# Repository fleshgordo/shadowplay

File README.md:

---------------------------------------------------------------

TIAN shadowplay - robotic light installation

Copyright Gordan Savicic 2012.

This program is free software: you can redistribute it
and/or modify it under the terms of the GNU Lesser General
Public License as published by the Free Software Foundation,
either version 3 of the License, or (at your option) any 
later version.

This program is distributed in the hope that it will be
useful, but WITHOUT ANY WARRANTY; without even the implied
warranty of MERCHANTABILITY or FITNESS FOR A PARTICULAR
PURPOSE.  See the GNU Lesser General Public License for more
details.

You should have received a copy of the GNU Lesser General
Public License along with this program.  If not, see
<http://www.gnu.org/licenses/>.

---------------------------------------------------------------

Shadowplay is a light installation for TIAN's chandelier
(www.tian-vienna.com) 
Concept & Production by design agency STRUKT Vienna 
(www.strukt.com) 
Light Design & Hardware by Gordan Savicic 
(www.yugo.at)

Two pan/tilt robotic units equipped with 10W LEDs were
installed inside the chandelier.  Through algorithmic
controlling of light positioning and brightness (PWM), they
produce different shadows along the ceiling and walls,
inviting the participator to experience various
patterns and reflections which subsequently form
their own spatial narrative.

---------------------------------------------------------------

Main hardware parts (see /schematics folder for CAD files):

* Arduino Mega (www.arduino.cc/en/Main/ArduinoBoardMega)
* Wifi Shield (www.arduino.cc/en/Main/ArduinoWiFiShield)
* 10W warm-white LEDs (www.reichelt.de) Constant Current
* Drivers BUCK (www.led-tech.de) 
* Glass Lenses (Lens Reflector 10W www.hero-ledstore.com)
* Custom PCB 
* Custom Aluminium pan/tilt unit (see /cnc folder for drawings)
  based on Lynx B Pan and Tilt kit (www.lynxmotion.com)

Software:

* written in C (see /firmware folder)

---------------------------------------------------------------

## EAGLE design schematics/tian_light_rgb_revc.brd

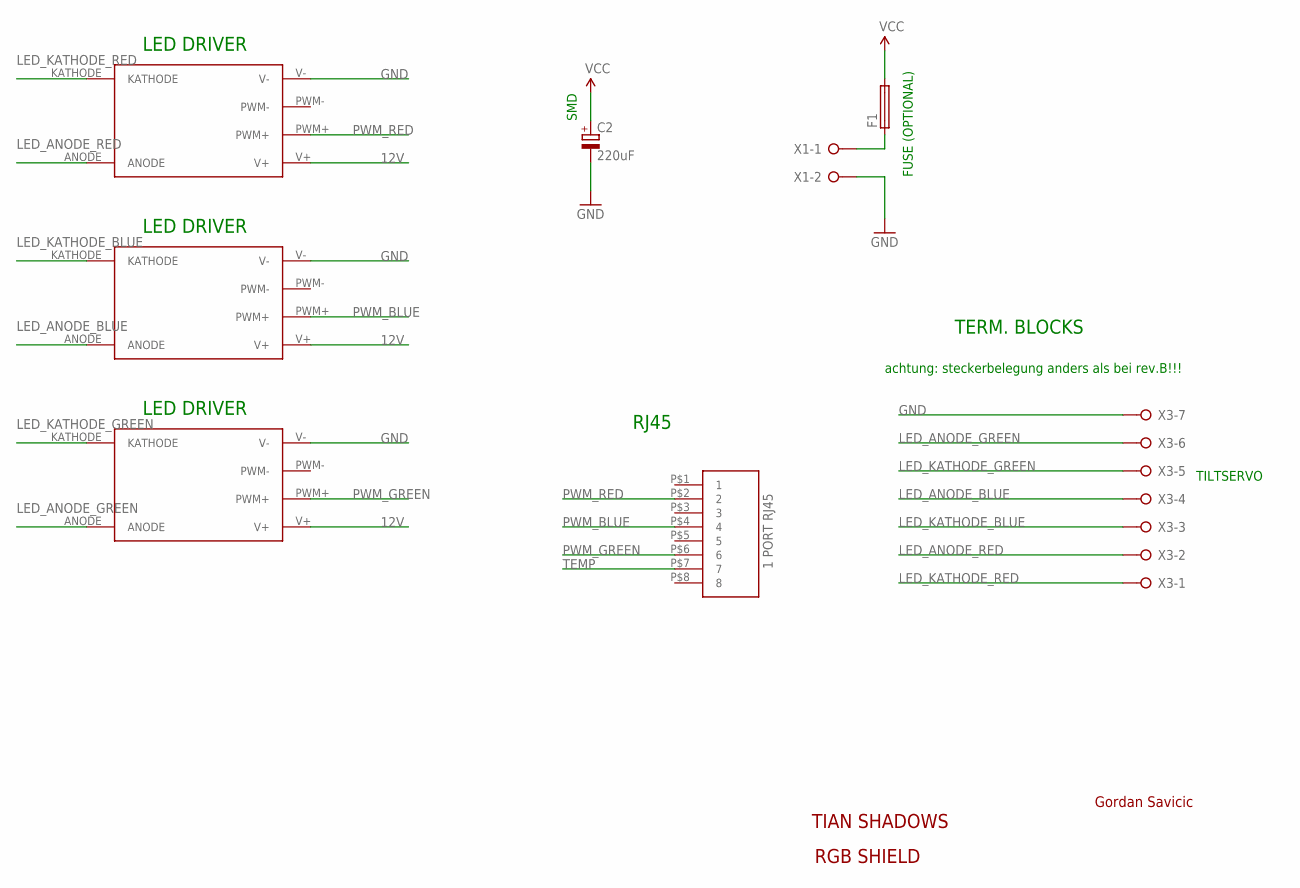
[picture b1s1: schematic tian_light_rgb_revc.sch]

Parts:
C2: 220uF; PANASONIC_F
F1: SH22,5
U$1, U$2, U$3: BUCK_LED_DRIVER
U$5: 1PORT_ETHERNET
X1: W237-02P; W237-132
X3: W237-07P; W237-7P

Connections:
12V: C2.+, F1.2, U$1.V+, U$2.V+, U$3.V+
GND: C2.-, U$1.V-, U$2.V-, U$3.V-, X1.2, X3.7
LED_ANODE_BLUE: U$2.ANODE, X3.4
LED_ANODE_GREEN: U$3.ANODE, X3.6
LED_ANODE_RED: U$1.ANODE, X3.2
LED_KATHODE_BLUE: U$2.KATHODE, X3.3
LED_KATHODE_GREEN: U$3.KATHODE, X3.5
LED_KATHODE_RED: U$1.KATHODE, X3.1
unnamed: F1.1, X1.1
PWM_BLUE: U$2.PWM+, U$5.P$4 (4)
PWM_GREEN: U$3.PWM+, U$5.P$6 (6)
PWM_RED: U$1.PWM+, U$5.P$2 (2)
TEMP: U$5.P$7 (7)

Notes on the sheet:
TILTSERVO
TIAN SHADOWS
RGB SHIELD
Gordan Savicic
RJ45
TERM. BLOCKS
LED DRIVER
achtung: steckerbelegung anders als bei rev.B!!!
FUSE (OPTIONAL)
SMD

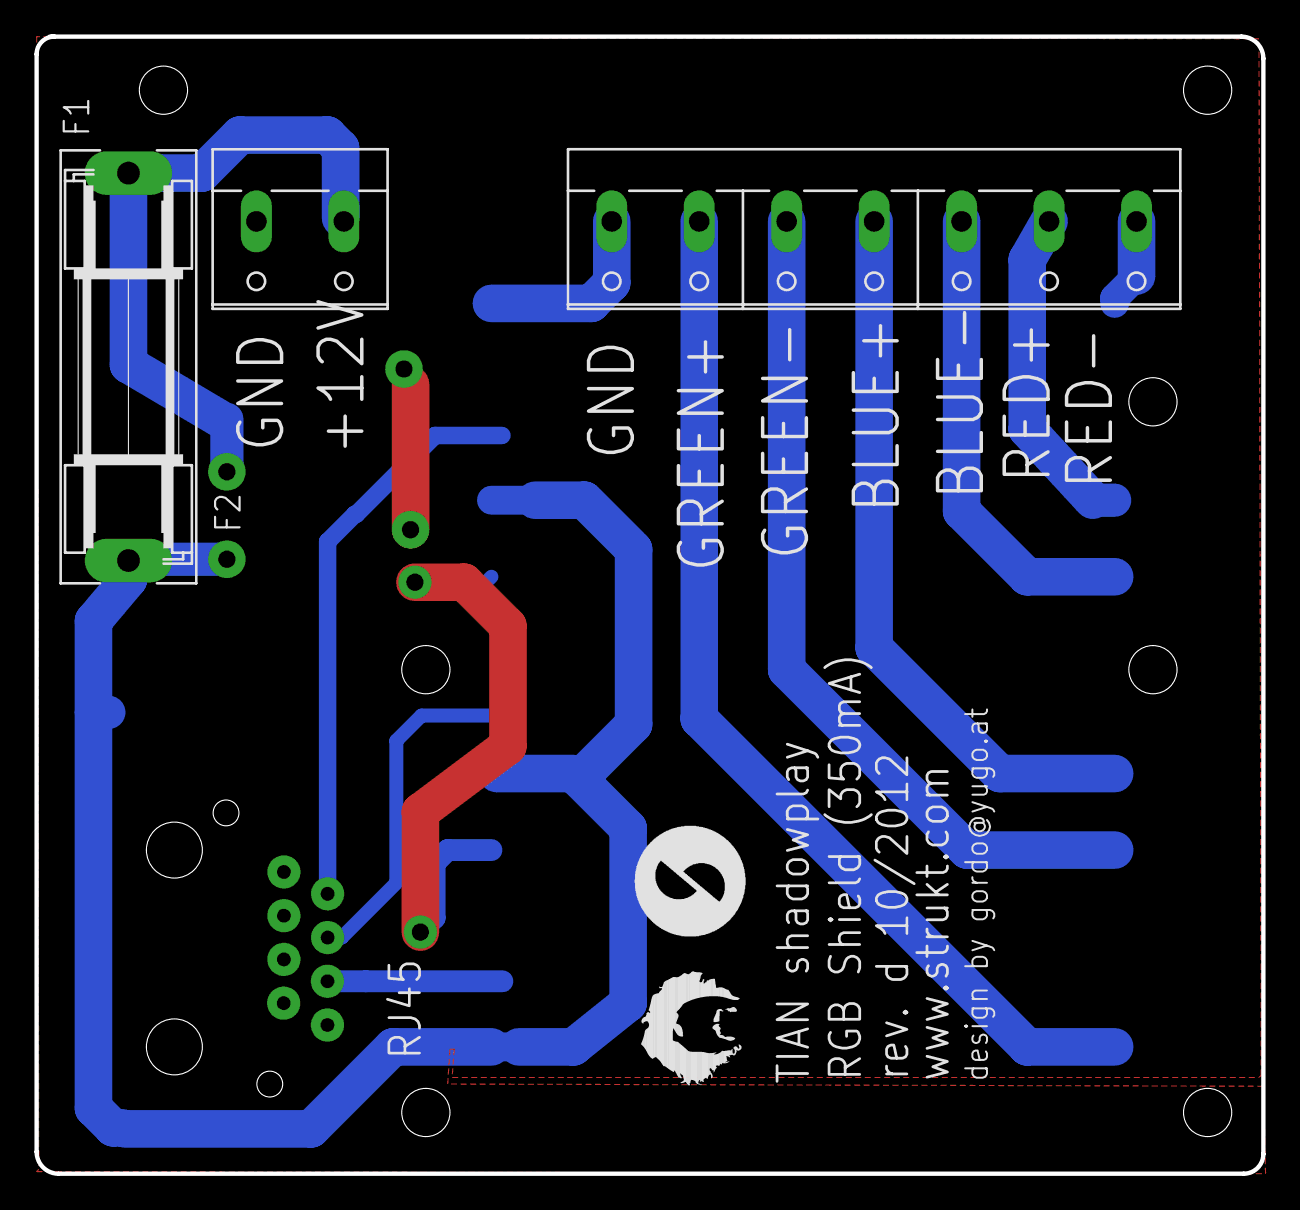
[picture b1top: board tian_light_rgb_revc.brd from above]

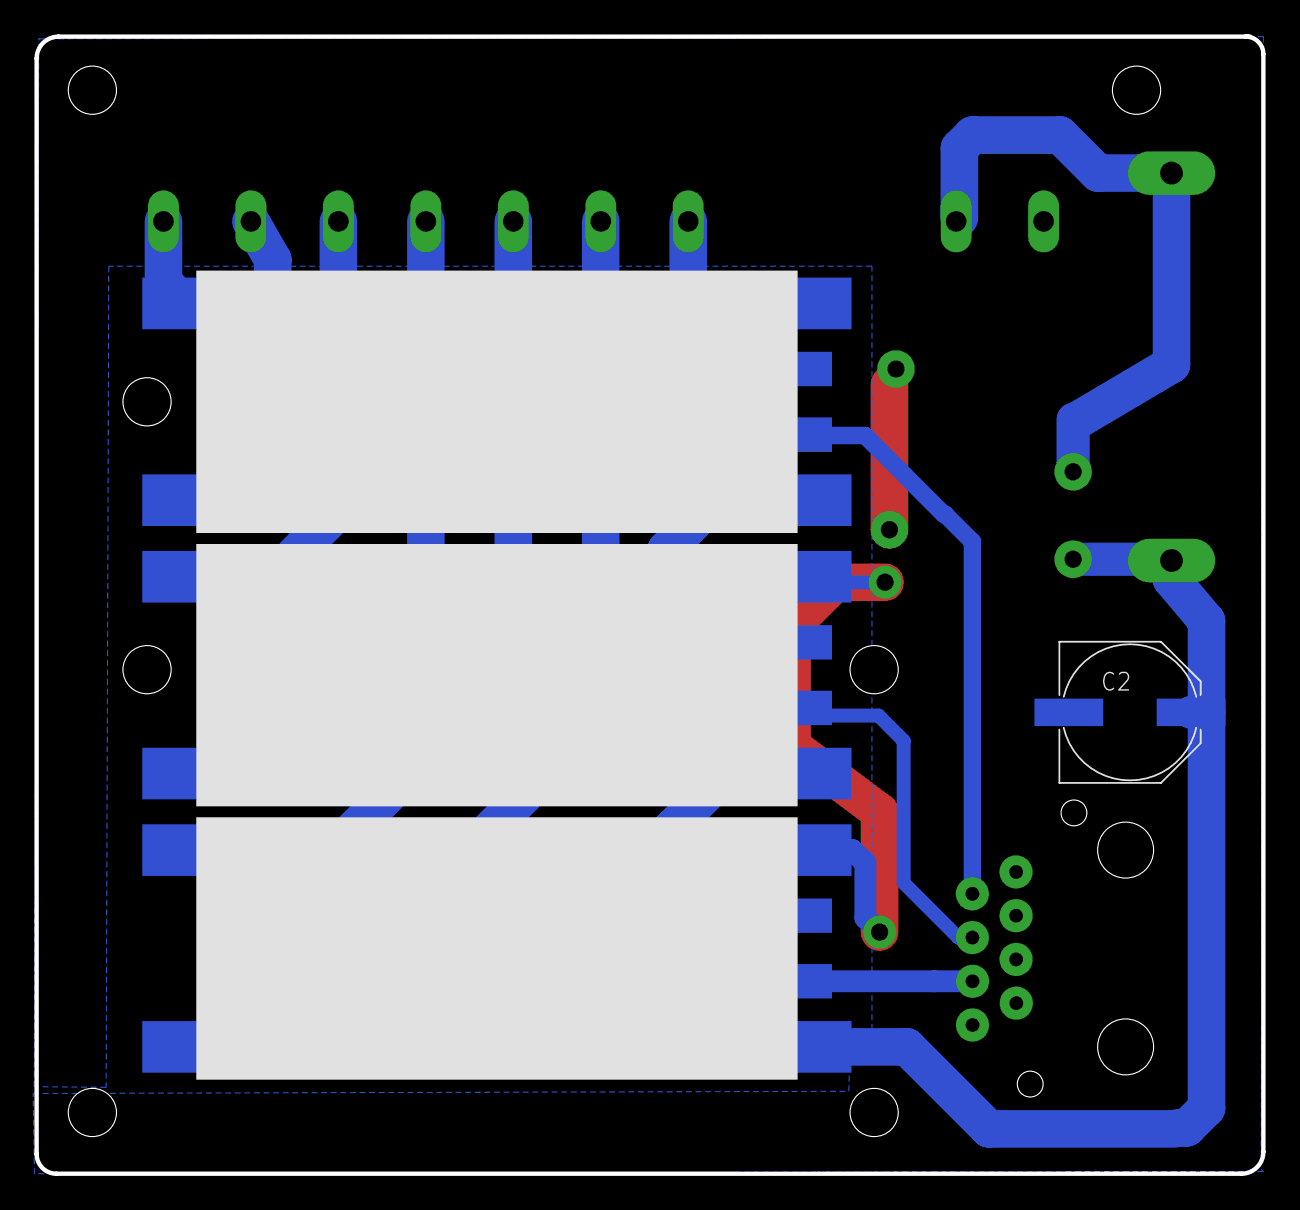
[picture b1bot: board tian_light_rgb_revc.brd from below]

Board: 2 copper layers, 71.2 x 66.0 mm, 8 parts (5 on the bottom side), 12 nets.

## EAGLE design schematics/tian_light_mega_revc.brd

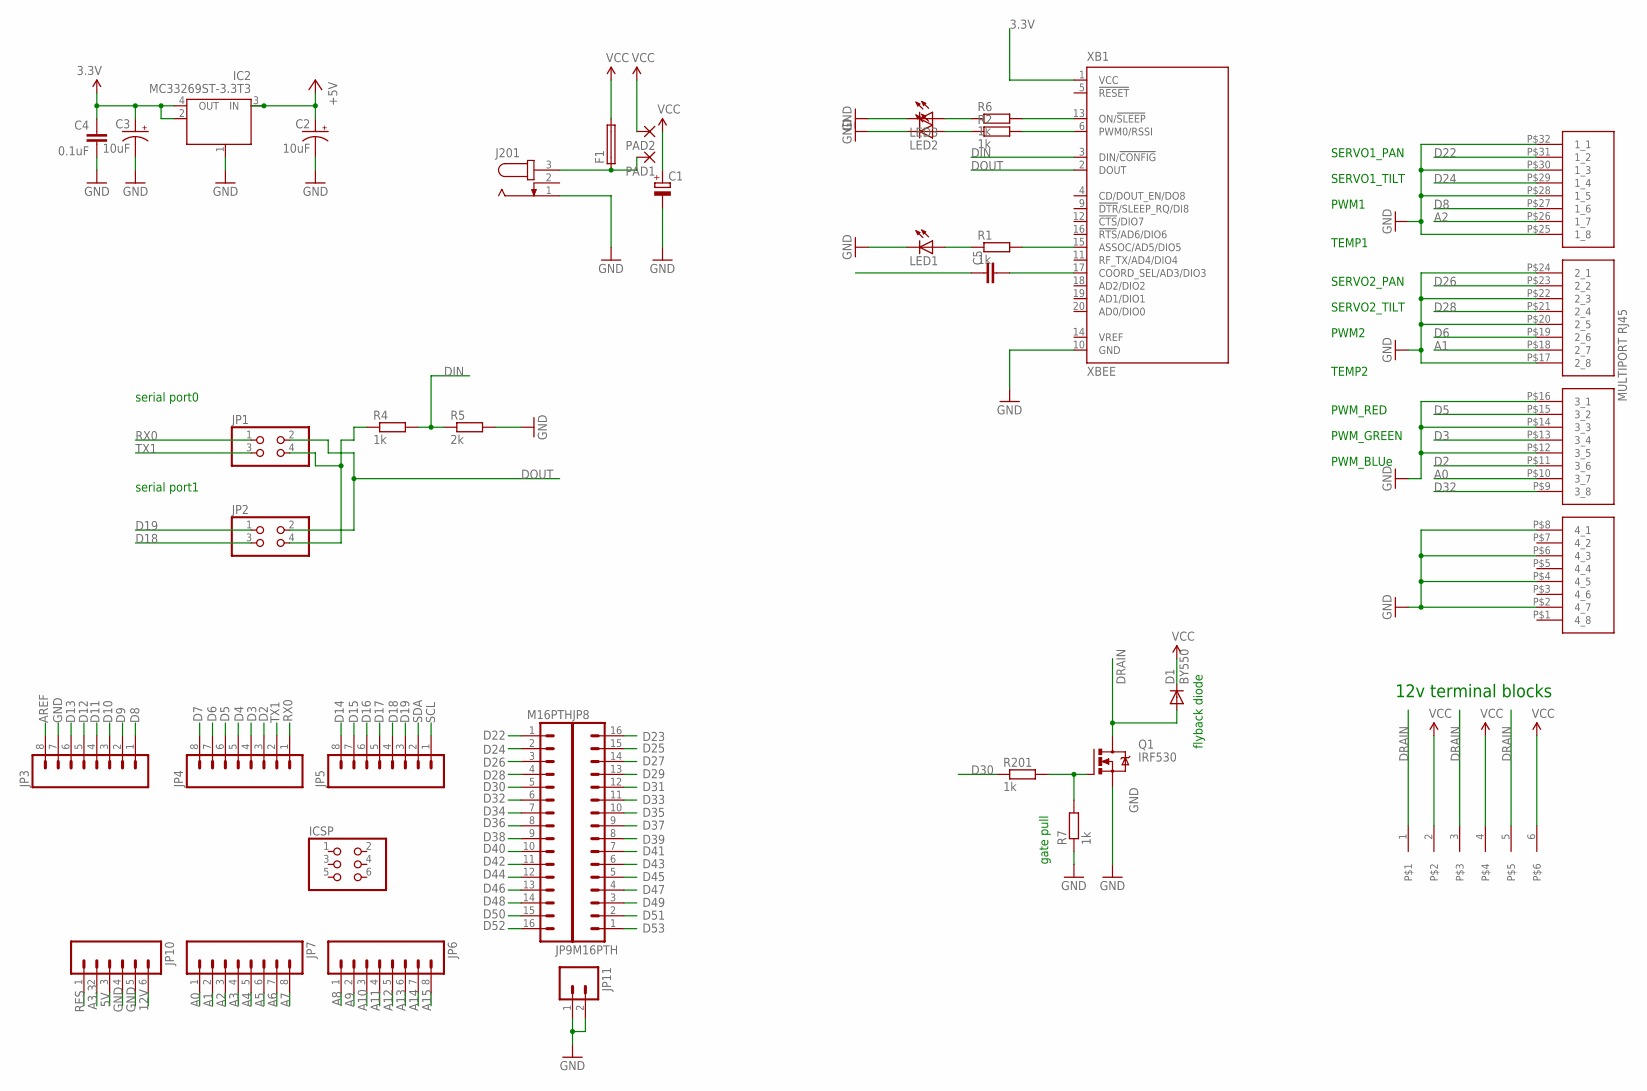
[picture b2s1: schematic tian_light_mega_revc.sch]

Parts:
C1: CPOL-EU153CLV-0605; 153CLV-0605
C2, C3: 10uF; EIA3216
C4: 0.1uF; 0603-CAP
C5: C-EUC0805; C0805
D1: BY550; DO27-15
F1: SH22,5
IC2: MC33269ST-3.3T3; SOT223
ICSP: PINHD-2X3; 2X03
J201: JACK-PLUG0; SPC4077
JP1, JP2: PINHD-2X2; 2X02
JP3, JP4, JP5, JP6, JP7: M08LONGPADS; 1X08_LONGPADS
JP8, JP9: M16PTH; 1X16
JP10: M06SIP; 1X06
JP11: M02LOCK; 1X02_LOCK
LED1, LED2, LED3: LEDSML1206; SML1206
PAD1, PAD2: 2,15/1,0
PORT201: 4PORT_ETHERNET
Q1: IRF530; TO220BV
R1, R2, R4, R6, R7, R201: 1k; M1206
R5: 2k; M1206
U$3: MFKDSP6-5.08; PHONEIX
XB1: XBEE

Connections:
3.3V: C3.A (+), C4.1, IC2.2 (OUT), IC2.4 (OUT), XB1.1 (VCC)
5V: C2.A (+), IC2.3 (IN), JP10.3
12V: C1.+, F1.2, JP10.6, PAD2.1, U$3.2, U$3.4, U$3.6
A0: JP7.1, PORT201.P$10 (3_7)
A1: JP7.2, PORT201.P$18 (2_7)
A2: JP7.3, PORT201.P$26 (1_7)
A3: JP7.4
A3.3: JP10.2
A4: JP7.5
A5: JP7.6
A6: JP7.7
A7: JP7.8
A8: JP6.1
A9: JP6.2
A10: JP6.3
A11: JP6.4
A12: JP6.5
A13: JP6.6
A14: JP6.7
A15: JP6.8
AREF: JP3.8
D2: JP4.3, PORT201.P$11 (3_6)
D3: JP4.4, PORT201.P$13 (3_4)
D4: JP4.5
D5: JP4.6, PORT201.P$15 (3_2)
D6: JP4.7, PORT201.P$19 (2_6)
D7: JP4.8
D8: JP3.1, PORT201.P$27 (1_6)
D9: JP3.2
D10: JP3.3
D11: JP3.4
D12: JP3.5
D13: JP3.6
D14: JP5.8
D15: JP5.7
D16: JP5.6
D17: JP5.5
D18: JP2.3, JP5.4
D19: JP2.1, JP5.3
D22: JP9.1, PORT201.P$31 (1_2)
D23: JP8.16
D24: JP9.2, PORT201.P$29 (1_4)
D25: JP8.15
D26: JP9.3, PORT201.P$23 (2_2)
D27: JP8.14
D28: JP9.4, PORT201.P$21 (2_4)
D29: JP8.13
D30: JP9.5, R201.1
D31: JP8.12
D32: JP9.6, PORT201.P$9 (3_8)
D33: JP8.11
D34: JP9.7
D35: JP8.10
D36: JP9.8
D37: JP8.9
D38: JP9.9
D39: JP8.8
D40: JP9.10
D41: JP8.7
D42: JP9.11
D43: JP8.6
D44: JP9.12
D45: JP8.5
D46: JP9.13
D47: JP8.4
D48: JP9.14
D49: JP8.3
D50: JP9.15
D51: JP8.2
D52: JP9.16
D53: JP8.1
DIN: R4.2, R5.1, XB1.3 (DIN/!CONFIG)
DOUT: JP1.2, JP2.2, XB1.2 (DOUT)
DRAIN: D1.A, Q1.D, U$3.1, U$3.3, U$3.5
GND: C1.-, C2.C (-), C3.C (-), C4.2, IC2.1 (GND/ADJ), J201.1, JP3.7, JP10.4, JP10.5, JP11.1, JP11.2, LED1.C, LED2.C, LED3.C, PORT201.P$2 (4_7), PORT201.P$4 (4_5), PORT201.P$6 (4_3), PORT201.P$8 (4_1), PORT201.P$12 (3_5), PORT201.P$14 (3_3), PORT201.P$16 (3_1), PORT201.P$17 (2_8), PORT201.P$20 (2_5), PORT201.P$22 (2_3), PORT201.P$24 (2_1), PORT201.P$25 (1_8), PORT201.P$28 (1_5), PORT201.P$30 (1_3), PORT201.P$32 (1_1), Q1.S, R5.2, R7.1, XB1.10 (GND)
unnamed: JP1.4, JP2.4, R4.1
unnamed: LED1.A, R1.1
unnamed: Q1.G, R7.2, R201.2
unnamed: R1.2, XB1.15 (ASSOC/AD5/DIO5)
unnamed: R6.2, XB1.13 (ON/!SLEEP)
unnamed: LED2.A, R2.1
unnamed: R2.2, XB1.6 (PWM0/RSSI)
unnamed: LED3.A, R6.1
unnamed: C5.2, XB1.17 (COORD_SEL/AD3/DIO3)
unnamed: F1.1, J201.3, PAD1.1
RES: C5.1, JP10.1
RX0: JP1.1, JP4.1
SCL: JP5.1
SDA: JP5.2
TX1: JP1.3, JP4.2
VCC: D1.C

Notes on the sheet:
12v terminal blocks
SERVO1_PAN
SERVO1_TILT
PWM1
TEMP1
SERVO2_PAN
SERVO2_TILT
PWM2
TEMP2
PWM_RED
PWM_GREEN
PWM_BLUe
flyback diode
gate pull
serial port1
serial port0

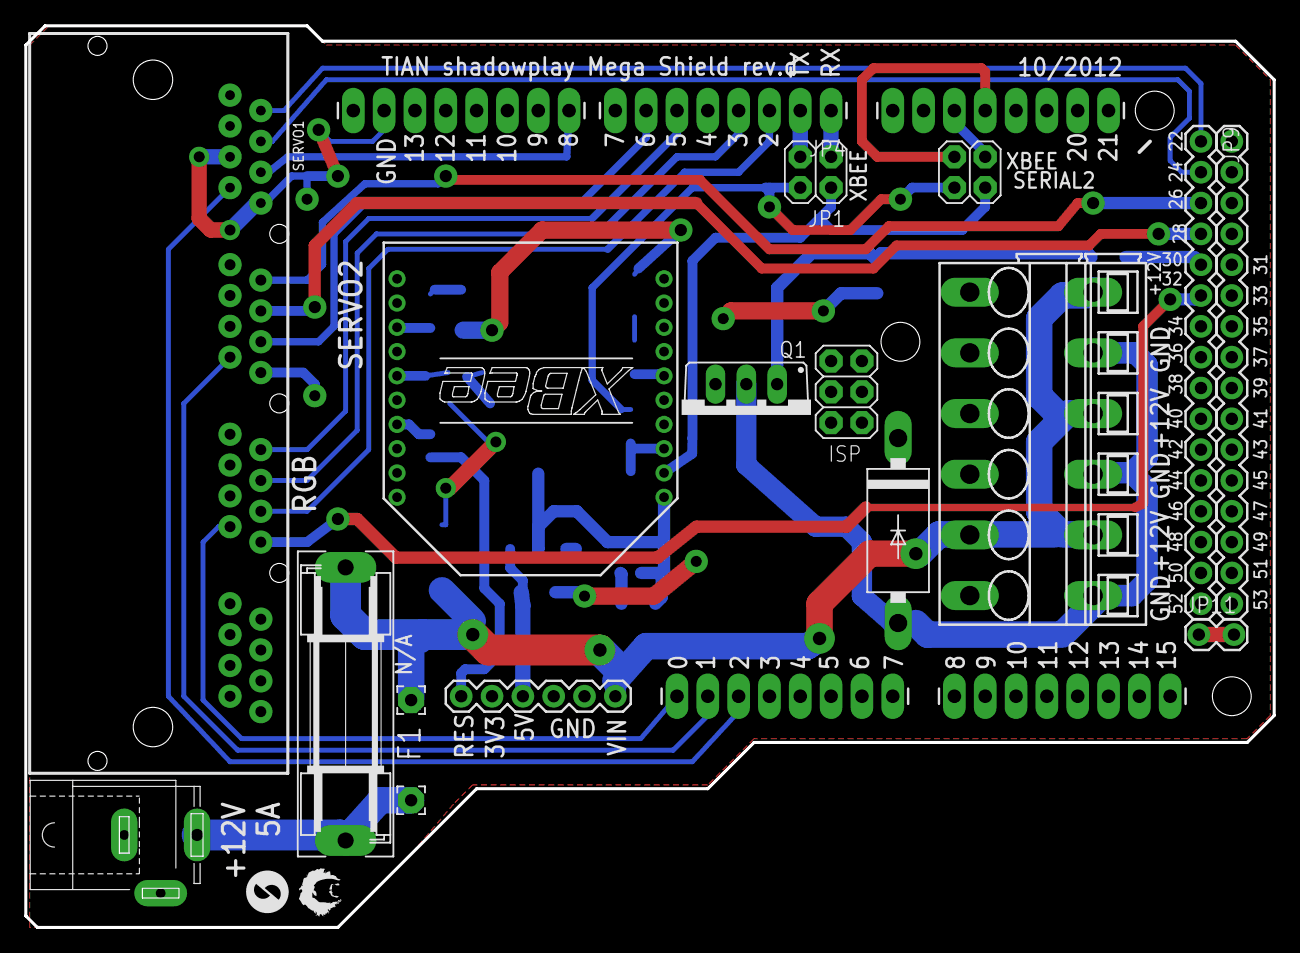
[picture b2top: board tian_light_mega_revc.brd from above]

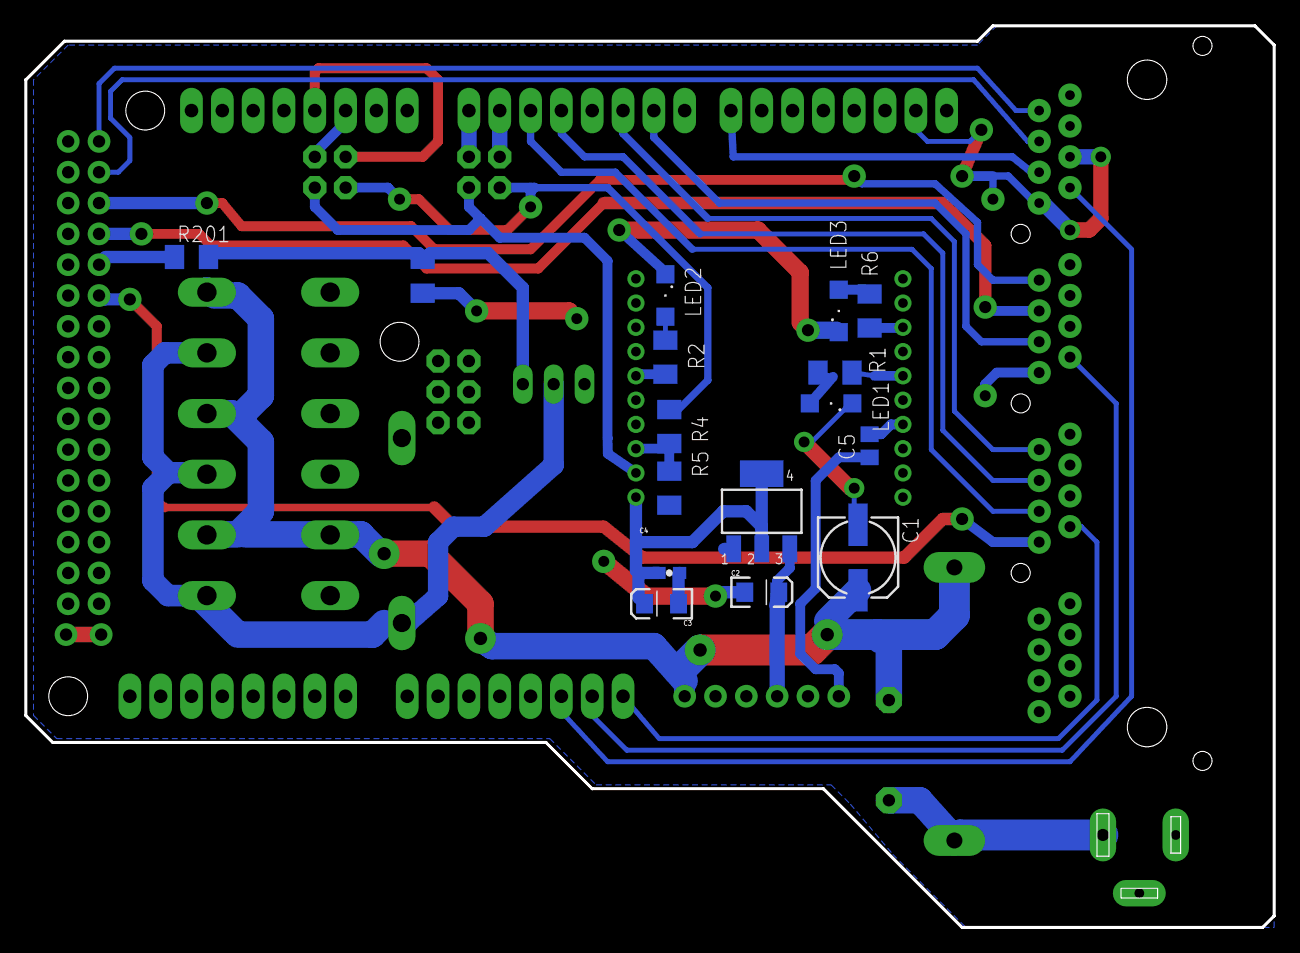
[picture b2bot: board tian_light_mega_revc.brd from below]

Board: 2 copper layers, 102.9 x 74.3 mm, 37 parts (16 on the bottom side), 36 nets.

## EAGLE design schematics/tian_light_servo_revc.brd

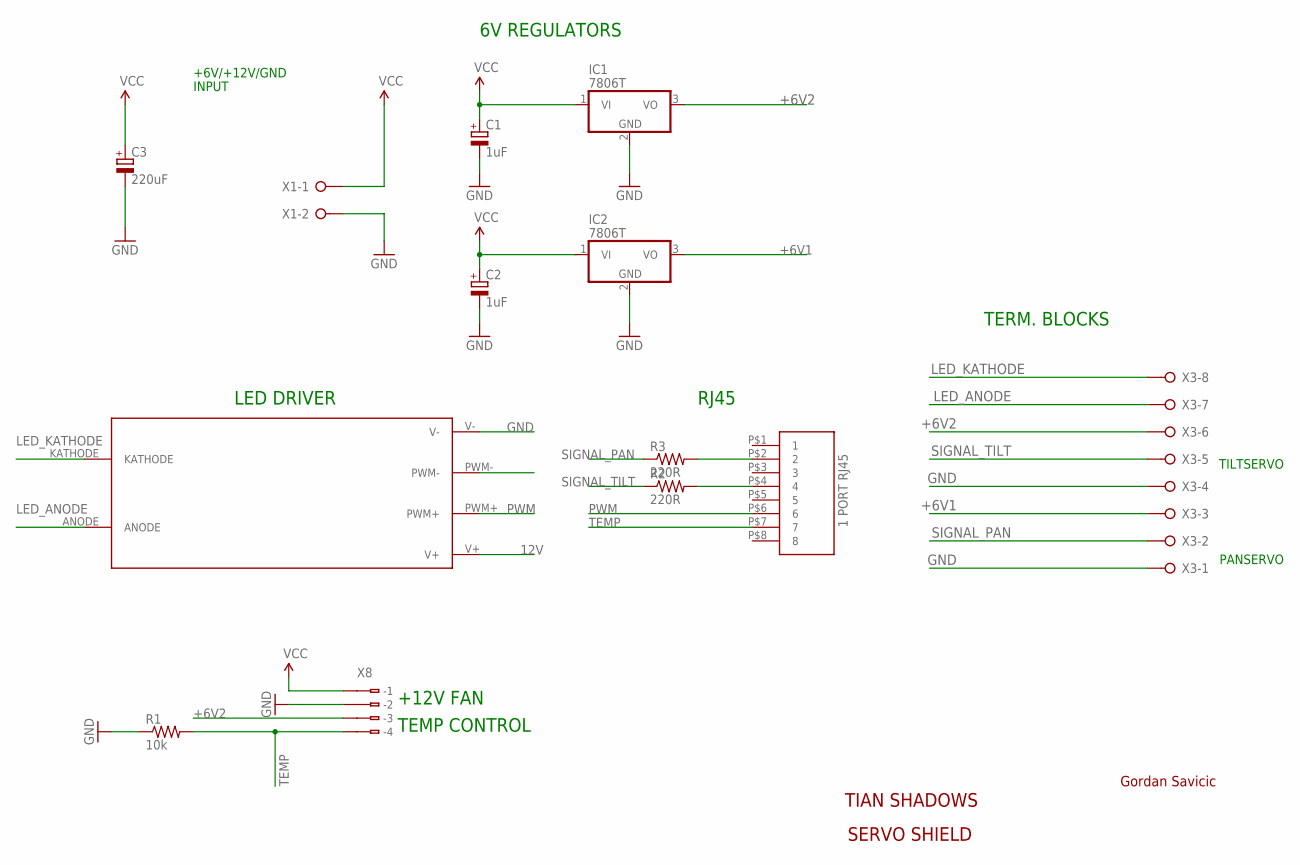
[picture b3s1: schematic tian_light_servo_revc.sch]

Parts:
C1, C2: 1uF; SMC_C
C3: 220uF; 153CLV-0605
IC1, IC2: 7806T; TO220H
R1: 10k; 1206
R2, R3: 220R; 1206
U$1: BUCK_LED_DRIVER
U$5: 1PORT_ETHERNET
X1: W237-02P; W237-132
X3: W237-08P; W237-8P
X8: 233-104

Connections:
12V: C1.+, C2.+, C3.+, IC1.1 (VI), IC2.1 (VI), U$1.V+, X1.1, X8.B1 (B-1)
+6V1: IC2.3 (VO), X3.3
+6V2: IC1.3 (VO), X3.6, X8.B3 (B-3)
GND: C1.-, C2.-, C3.-, IC1.2 (GND), IC2.2 (GND), R1.1, U$1.V-, X1.2, X3.1, X3.4, X8.B2 (B-2)
LED_ANODE: U$1.ANODE, X3.7
LED_KATHODE: U$1.KATHODE, X3.8
unnamed: R2.2, U$5.P$4 (4)
unnamed: R3.2, U$5.P$2 (2)
PWM: U$1.PWM+, U$5.P$6 (6)
SIGNAL_PAN: R3.1, X3.2
SIGNAL_TILT: R2.1, X3.5
TEMP: R1.2, U$5.P$7 (7), X8.B4 (B-4)

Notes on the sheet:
+6V/+12V/GND
INPUT
+12V FAN
TEMP CONTROL
PANSERVO
TILTSERVO
TIAN SHADOWS
SERVO SHIELD
Gordan Savicic
6V REGULATORS
RJ45
TERM. BLOCKS
LED DRIVER

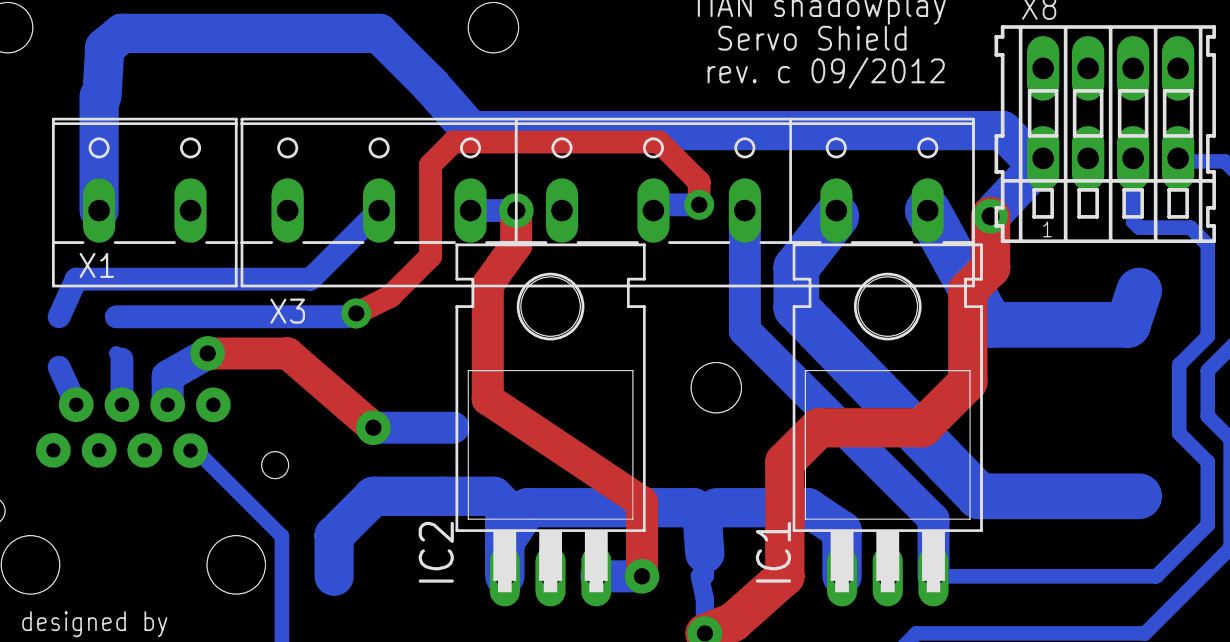
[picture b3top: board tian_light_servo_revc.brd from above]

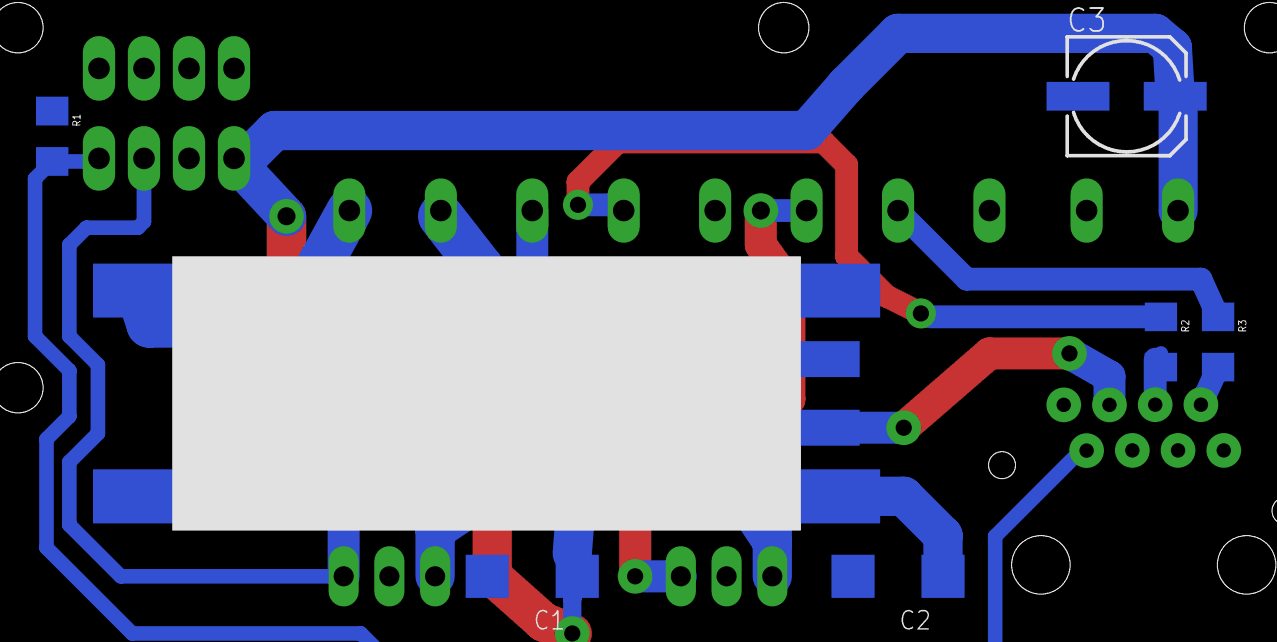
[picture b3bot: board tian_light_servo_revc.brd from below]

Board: 2 copper layers, 13 parts (8 on the bottom side), 12 nets.

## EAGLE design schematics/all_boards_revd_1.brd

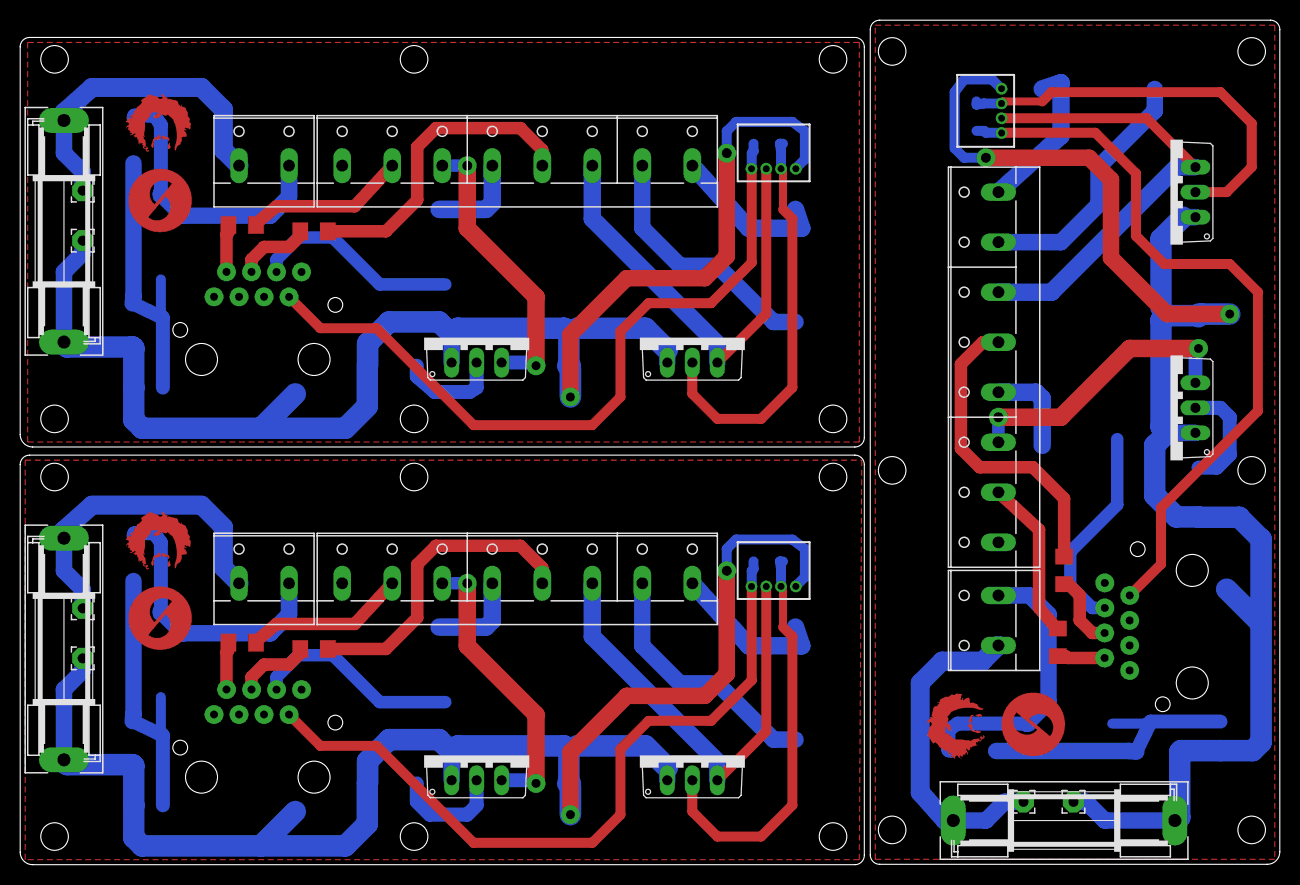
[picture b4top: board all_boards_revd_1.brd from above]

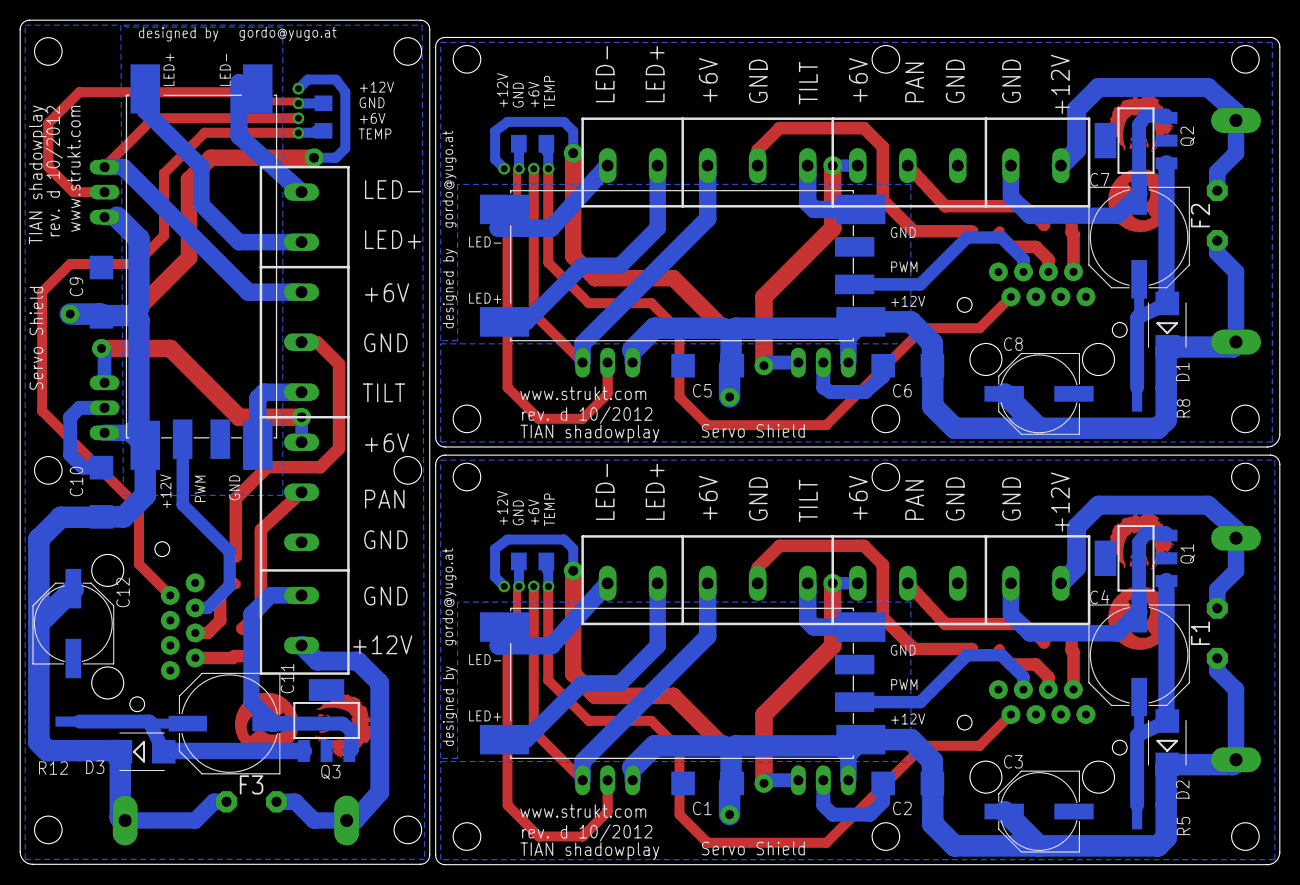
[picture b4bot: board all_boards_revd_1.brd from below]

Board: 2 copper layers, 127.9 x 85.8 mm, 60 parts (30 on the bottom side), 45 nets.

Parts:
C1, C2, C5, C6, C9, C10: 1uF; SMC_C
C3, C8, C12: 220uF; PANASONIC_F
C4, C7, C11: 10-20uF; PANASONIC_G
D1, D2, D3: ES2D; SMB
F1, F2, F3: SH22,5
IC1, IC2, IC3, IC4, IC5, IC6: 7805TV; TO220V
PAD1, PAD2, PAD3, PAD4, PAD5, PAD6: 2,15/1,0
Q1, Q2, Q3: N-HEXFET-2D_SOT232-; SOT223
R1, R4, R9: 10k; 1206
R2, R3, R6, R7, R10, R11: 220R; 1206
R5, R8, R12: 470k; R1218
U$1, U$2, U$4: BUCK_LED_DRIVER
U$3, U$5, U$6: 1PORT_ETHERNET
X1, X5, X8: W237-132
X2, X3, X7: W237-8P
X4, X6, X9: S4B-ZR

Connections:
12V: C1.+, C2.+, C3.+, D2.C, F1.2, IC3.1, IC4.1, PAD1.1, R5.2, U$1.V+, X4.1
12V1: C5.+, C6.+, C8.+, D1.C, F2.2, IC1.1, IC2.1, PAD3.1, R8.2, U$2.V+, X6.1
12V2: C9.+, C10.+, C12.+, D3.C, F3.2, IC5.1, IC6.1, PAD5.1, R12.2, U$4.V+, X9.1
+6V1: IC4.3, X3.3
+6V2: IC3.3, X3.6, X4.3
+6V3: IC1.3, X2.6, X6.3
+6V4: IC2.3, X2.3
+6V5: IC5.3, X7.6, X9.3
+6V6: IC6.3, X7.3
GND: C1.-, C2.-, C3.-, IC3.2, IC4.2, Q1.2, Q1.4, R1.1, U$1.V-, X3.1, X3.4, X4.2
GND1: C5.-, C6.-, C8.-, IC1.2, IC2.2, Q2.2, Q2.4, R4.1, U$2.V-, X2.1, X2.4, X6.2
GND2: C9.-, C10.-, C12.-, IC5.2, IC6.2, Q3.2, Q3.4, R9.1, U$4.V-, X7.1, X7.4, X9.2
GND_INPUT: C4.-, Q1.3, X1.2
GND_INPUT1: C7.-, Q2.3, X5.2
GND_INPUT2: C11.-, Q3.3, X8.2
LED_ANODE: U$1.ANODE, X3.7
LED_ANODE1: U$2.ANODE, X2.7
LED_ANODE2: U$4.ANODE, X7.7
LED_KATHODE: U$1.KATHODE, X3.8
LED_KATHODE1: U$2.KATHODE, X2.8
LED_KATHODE2: U$4.KATHODE, X7.8
unnamed: R2.2, U$5.P$4
unnamed: R3.2, U$5.P$2
unnamed: C4.+, D2.A, Q1.1, R5.1
unnamed: F1.1, PAD2.1, X1.1
unnamed: R6.2, U$3.P$4
unnamed: R7.2, U$3.P$2
unnamed: C7.+, D1.A, Q2.1, R8.1
unnamed: F2.1, PAD4.1, X5.1
unnamed: R10.2, U$6.P$4
unnamed: R11.2, U$6.P$2
unnamed: C11.+, D3.A, Q3.1, R12.1
unnamed: F3.1, PAD6.1, X8.1
PWM: U$1.PWM+, U$5.P$6
PWM1: U$2.PWM+, U$3.P$6
PWM2: U$4.PWM+, U$6.P$6
SIGNAL_PAN: R3.1, X3.2
SIGNAL_PAN1: R7.1, X2.2
SIGNAL_PAN2: R11.1, X7.2
SIGNAL_TILT: R2.1, X3.5
SIGNAL_TILT1: R6.1, X2.5
SIGNAL_TILT2: R10.1, X7.5
TEMP: R1.2, U$5.P$7, X4.4
TEMP1: R4.2, U$3.P$7, X6.4
TEMP2: R9.2, U$6.P$7, X9.4

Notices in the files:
parts and their libraries:
SparkFun: Licensing: CC v3.0 Share-Alike You are welcome to use this library for commercial purposes.
